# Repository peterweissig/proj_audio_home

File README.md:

# project_audio_home
Simple audio project for sound system @home

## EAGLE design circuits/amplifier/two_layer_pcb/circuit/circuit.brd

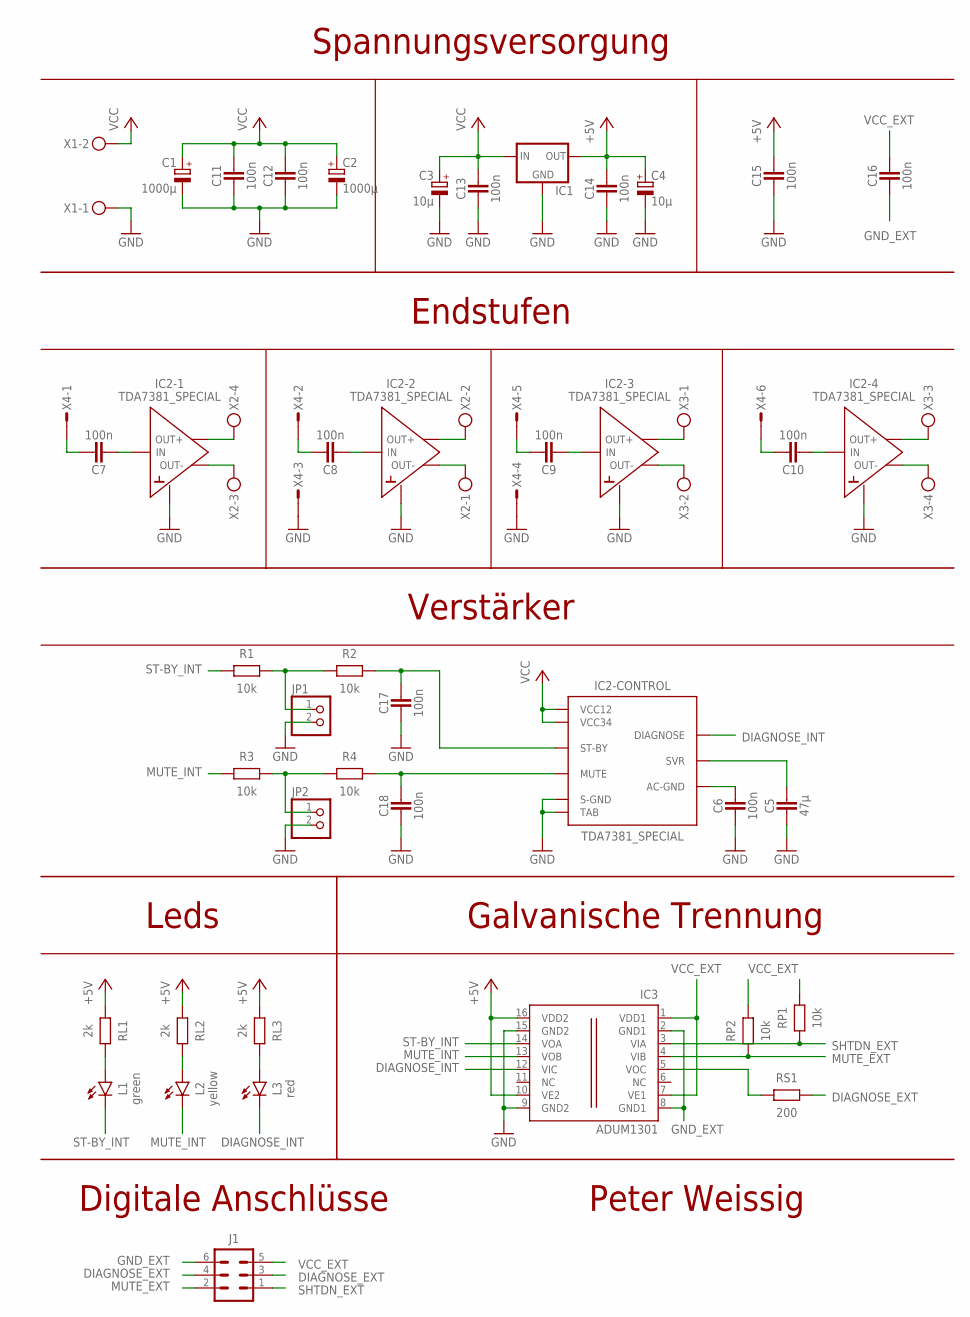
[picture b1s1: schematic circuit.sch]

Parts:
C1, C2: 1000µ; E5-10,5
C3, C4: 10µ; E2-5
C5: 47µ; SMD_2312S
C6, C11, C12, C13, C14, C15, C16: 100n; SMD_1206
C7, C8, C9, C10, C17, C18: 100n; C_THT_3
IC1: 78XXS
IC2: TDA7381_SPECIAL; IC_FLEXIWATT25_SPECIAL
IC3: ADUM1301; SO-16W
J1: STECKER_WANNE_6
JP1, JP2: PINHD-1X2; 1X02
L1: green; LED_3MM
L2: yellow; LED_3MM
L3: red; LED_3MM
R1, R2, R3, R4: 10k; SMD_1206
RL1, RL2, RL3: 2k; SMD_1206
RP1, RP2: 10k; SMD_1206
RS1: 200; SMD_1206
X1: STECKER_SPG_2
X2, X3: STECKER_SPG_4
X4: STECKER_MICROMATCH_6

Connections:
+5V: C4.+, C14.1, C15.1, IC1.OUT, IC3.10 (VE2), IC3.16 (VDD2), RL1.2, RL2.2, RL3.2
DIAGNOSE_EXT: J1.3, J1.4, RS1.2
DIAGNOSE_INT: IC2.25 (DIAGNOSE), IC3.12 (VIC), L3.K (C)
GND: C1.-, C2.-, C3.-, C4.-, C5.2, C6.2, C11.2, C12.2, C13.2, C14.2, C15.2, C17.1, C18.1, IC1.GND, IC2.1 (TAB), IC2.2 (GND), IC2.8 (GND), IC2.13 (S-GND), IC2.18 (GND), IC2.24 (GND), IC3.9 (GND2), IC3.15 (GND2), JP1.2, JP2.2, X1.1, X4.3, X4.4
GND_EXT: C16.2, IC3.2 (GND1), IC3.8 (GND1), J1.6
MUTE: C18.2, IC2.22 (MUTE), R4.2
MUTE_EXT: IC3.4 (VIB), J1.2, RP2.1
MUTE_INT: IC3.13 (VOB), L2.K (C), R3.1
unnamed: C7.2, IC2.11 (IN)
unnamed: C7.1, X4.1
unnamed: C8.1, X4.2
unnamed: C8.2, IC2.12 (IN)
unnamed: C9.1, X4.5
unnamed: C10.1, X4.6
unnamed: C9.2, IC2.15 (IN)
unnamed: C10.2, IC2.14 (IN)
unnamed: JP1.1, R1.2, R2.1
unnamed: C5.1, IC2.10 (SVR)
unnamed: C6.1, IC2.16 (AC-GND)
unnamed: L3.A, RL3.1
unnamed: L1.A, RL1.1
unnamed: JP2.1, R3.2, R4.1
unnamed: L2.A, RL2.1
unnamed: IC3.5 (VOC), RS1.1
OUT1+: IC2.9 (OUT+), X2.4
OUT1-: IC2.7 (OUT-), X2.3
OUT2+: IC2.5 (OUT+), X2.2
OUT2-: IC2.3 (OUT-), X2.1
OUT3+: IC2.17 (OUT+), X3.1
OUT3-: IC2.19 (OUT-), X3.2
OUT4+: IC2.21 (OUT+), X3.3
OUT4-: IC2.23 (OUT-), X3.4
SHTDN_EXT: IC3.3 (VIA), J1.1, RP1.1
ST-BY: C17.2, IC2.4 (ST-BY), R2.2
ST-BY_INT: IC3.14 (VOA), L1.K (C), R1.1
VCC: C1.+, C2.+, C3.+, C11.1, C12.1, C13.1, IC1.IN, IC2.6 (VCC12), IC2.20 (VCC34), X1.2
VCC_EXT: C16.1, IC3.1 (VDD1), IC3.7 (VE1), J1.5, RP1.2, RP2.2

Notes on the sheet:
Spannungsversorgung
Peter Weissig
Endstufen
Digitale Anschlüsse
Galvanische Trennung
Verstärker
Leds

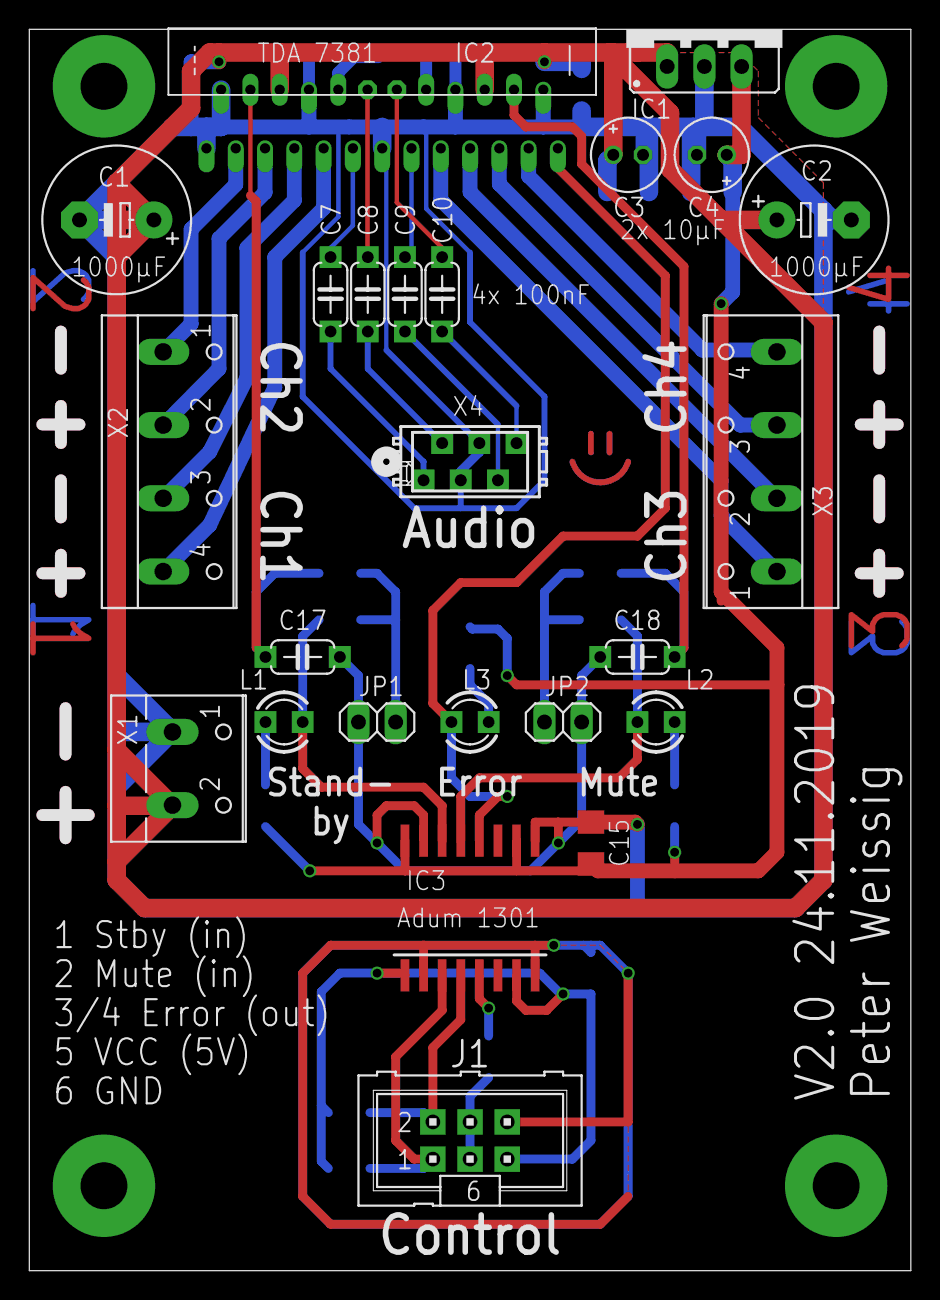
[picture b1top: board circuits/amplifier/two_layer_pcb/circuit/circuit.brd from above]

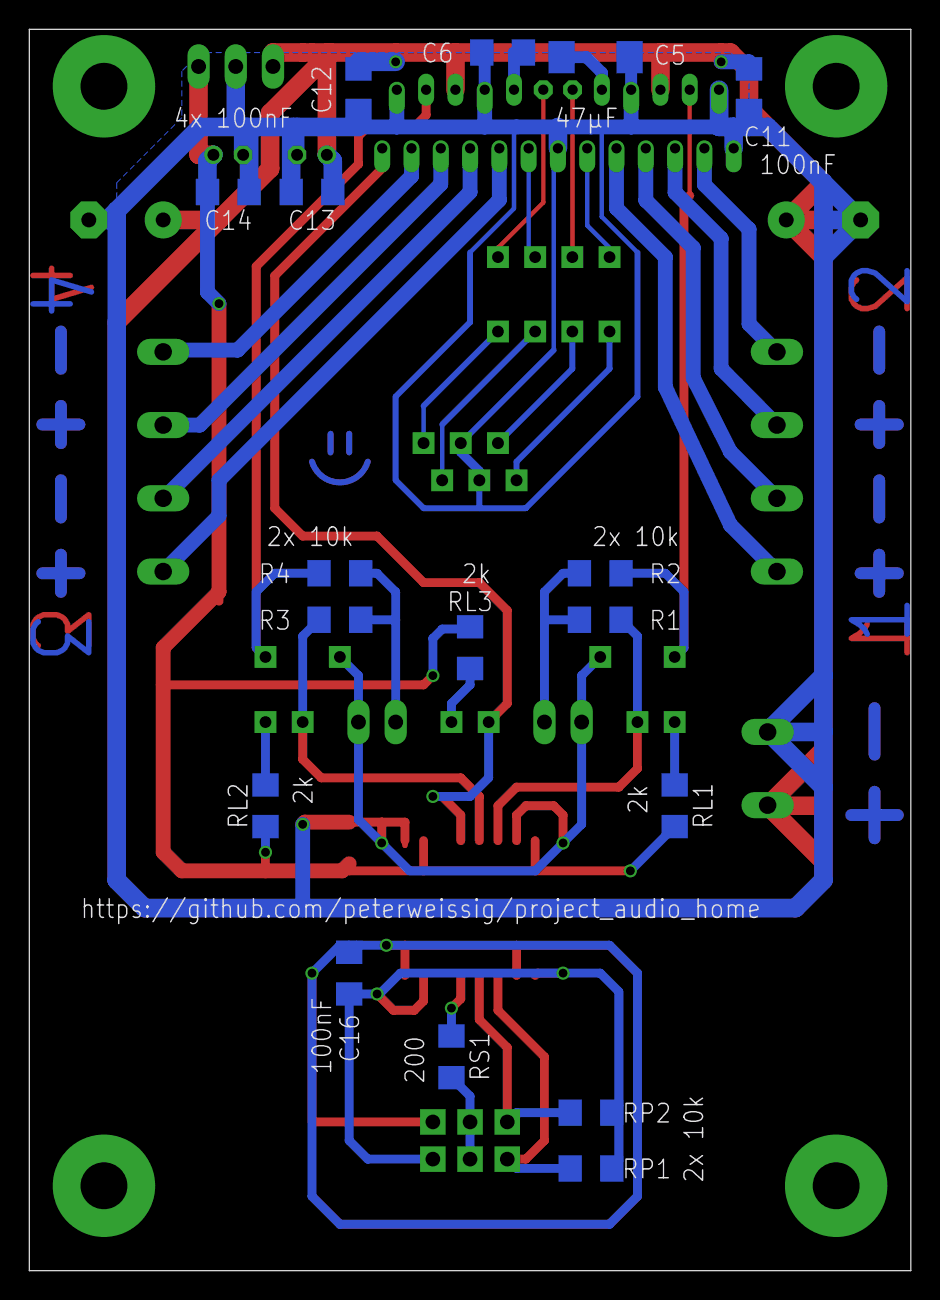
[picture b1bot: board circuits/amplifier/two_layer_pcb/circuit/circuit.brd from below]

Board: 2 copper layers, 60.2 x 84.8 mm, 41 parts (17 on the bottom side), 37 nets.

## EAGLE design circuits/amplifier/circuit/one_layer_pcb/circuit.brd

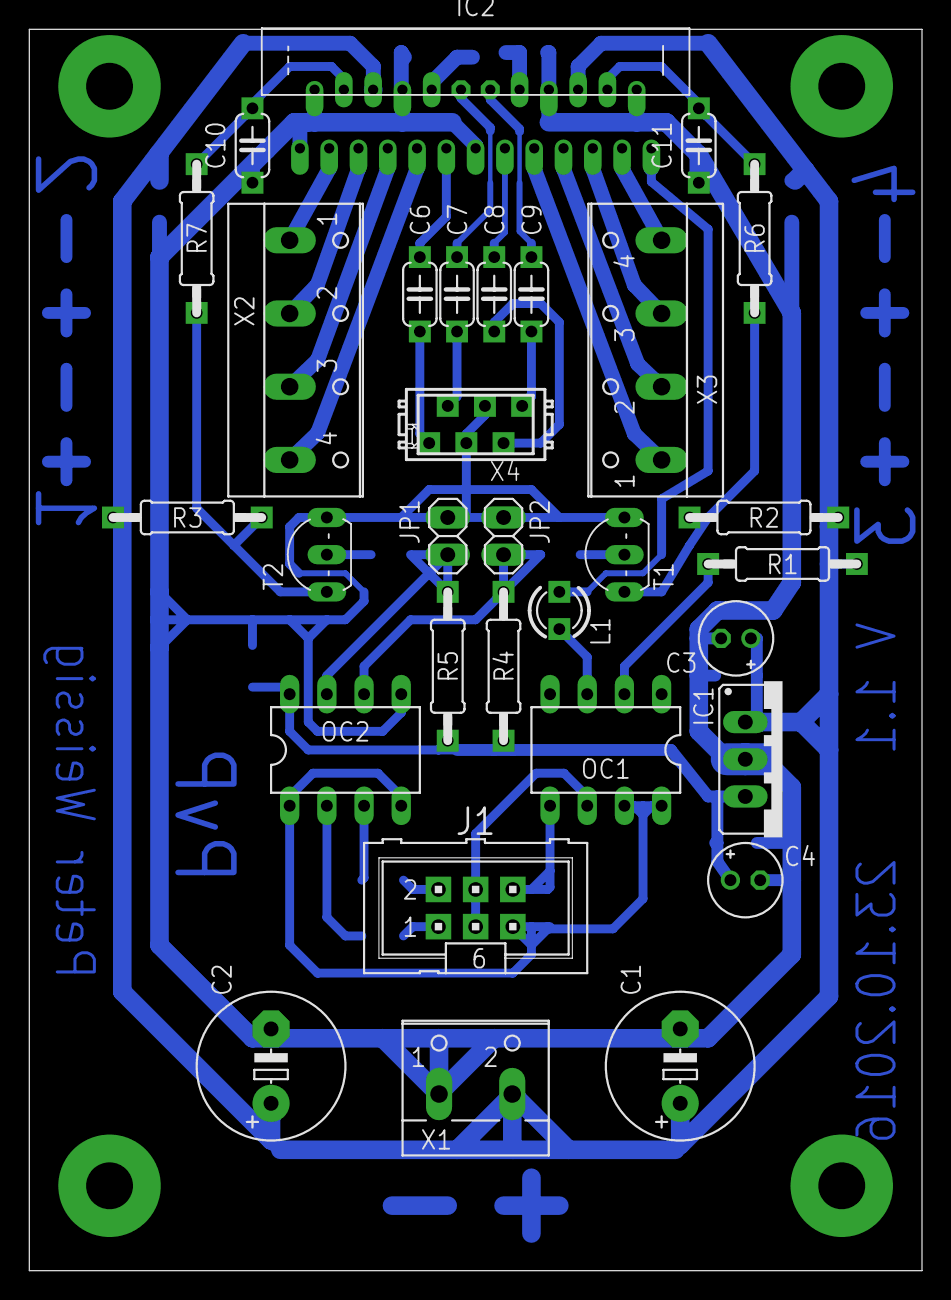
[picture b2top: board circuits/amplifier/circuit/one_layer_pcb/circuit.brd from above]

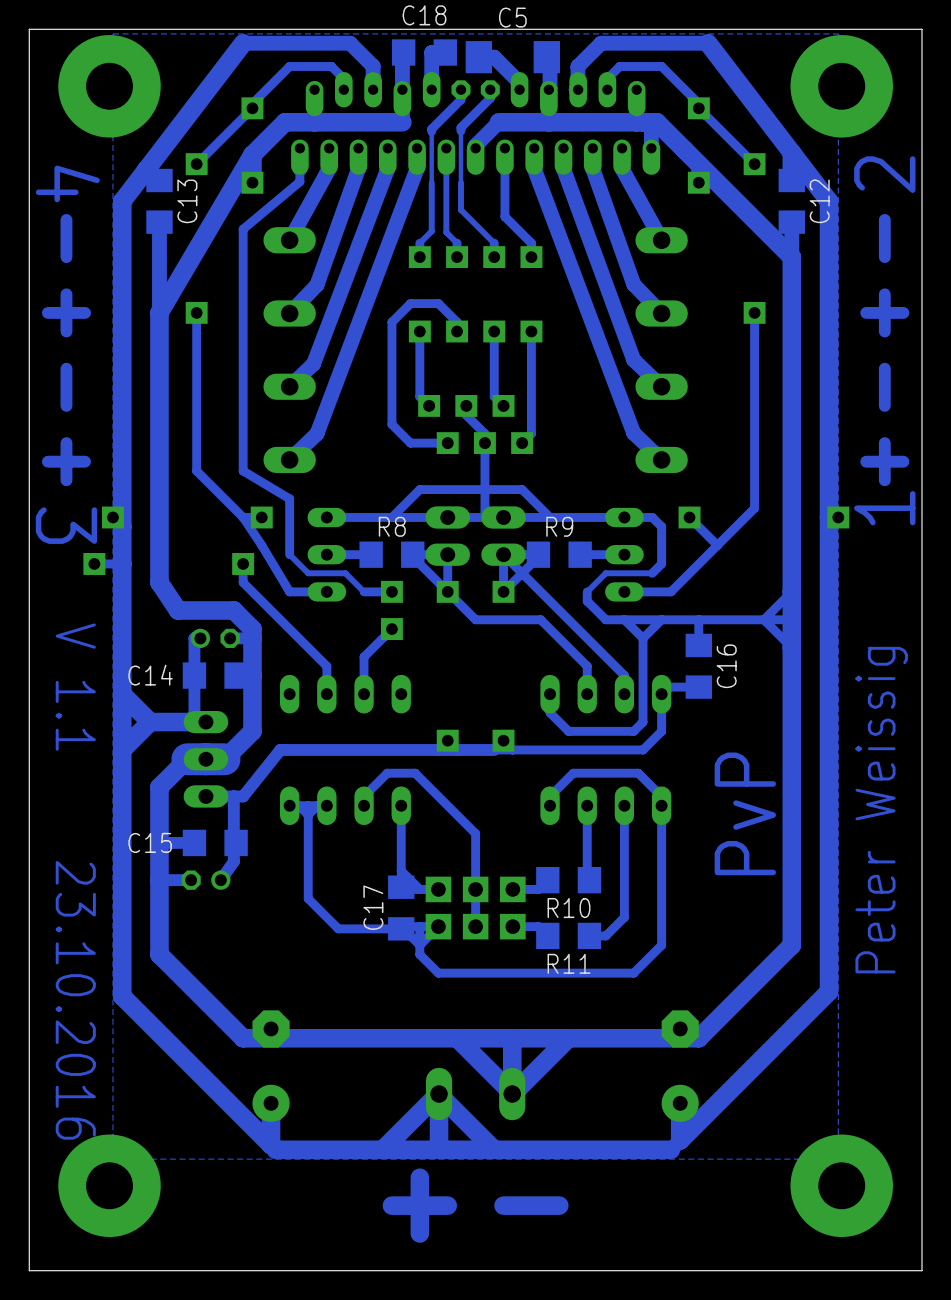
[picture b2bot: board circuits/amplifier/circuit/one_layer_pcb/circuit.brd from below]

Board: 2 copper layers, 61.0 x 84.8 mm, 43 parts (12 on the bottom side), 39 nets.

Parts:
C1, C2: 1000µ; E5-10,5
C3, C4: 10µ; E2-5
C5: 47µ; SMD_2312S
C6, C7, C8, C9, C10, C11: 100n; C_THT_3
C12, C13, C14, C15, C16, C17, C18: 100n; SMD_1206
IC1: 78XXS
IC2: TDA7381_SPECIAL; IC_FLEXIWATT25_SPECIAL
J1: STECKER_WANNE_6
JP1, JP2: 1X02
L1: LED_3MM
OC1: COUPLER_HCPL2601; IC_DIL08
OC2: COUPLER_HCPL2631; IC_DIL08
R1: 1k; R_THT_4
R2, R3, R4, R5, R6, R7: 10k; R_THT_4
R8, R9: 10k; SMD_1206
R10, R11: 150; SMD_1206
T1, T2: TO92-CBE
X1: STECKER_SPG_2
X2, X3: STECKER_SPG_4
X4: STECKER_MICROMATCH_6

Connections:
+5V: C4.+, C15.1, C16.1, IC1.OUT, OC2.8, R4.2, R5.2
DIAGNOSE_EXT: J1.3, J1.4, OC1.6
GND: C1.-, C2.-, C3.-, C4.-, C5.2, C10.1, C11.1, C12.2, C13.2, C14.2, C15.2, C16.2, C18.2, IC1.GND, IC2.1, IC2.2, IC2.8, IC2.13, IC2.18, IC2.24, JP1.1, JP2.1, OC2.5, T1.E, T2.E, X1.1, X4.3, X4.4
GND_EXT: C17.2, J1.6, OC1.5
MUTE_EXT: J1.2, R10.2
unnamed: C6.2, IC2.11
unnamed: C6.1, X4.1
unnamed: C7.1, X4.2
unnamed: C7.2, IC2.12
unnamed: C8.1, X4.5
unnamed: C9.1, X4.6
unnamed: C8.2, IC2.15
unnamed: C9.2, IC2.14
unnamed: C10.2, IC2.4, R7.1
unnamed: C11.2, IC2.22, R6.1
unnamed: C5.1, IC2.10
unnamed: C18.1, IC2.16
unnamed: IC2.25, L1.K
unnamed: L1.A, OC1.3
unnamed: R2.2, R6.2, T1.C
unnamed: JP2.2, OC2.6, R4.1, R8.1
unnamed: R8.2, T1.B
unnamed: OC1.2, R1.1
unnamed: R3.2, R7.2, T2.C
unnamed: JP1.2, OC2.7, R5.1, R9.1
unnamed: R9.2, T2.B
unnamed: OC2.2, R11.1
unnamed: OC2.3, R10.1
OUT1+: IC2.9, X2.4
OUT1-: IC2.7, X2.3
OUT2+: IC2.5, X2.2
OUT2-: IC2.3, X2.1
OUT3+: IC2.17, X3.1
OUT3-: IC2.19, X3.2
OUT4+: IC2.21, X3.3
OUT4-: IC2.23, X3.4
SHTDN_EXT: J1.1, R11.2
VCC: C1.+, C2.+, C3.+, C12.1, C13.1, C14.1, IC1.IN, IC2.6, IC2.20, R1.2, R2.1, R3.1, X1.2
VCC_EXT: C17.1, J1.5, OC1.7, OC1.8, OC2.1, OC2.4

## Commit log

2019-11-24 moved files of old one-sided pcb (audio-driver)
2019-11-24 added new two-sided version of audio-driver + exported images + exported elecrow-data + todo: part list
2019-11-24 updated gitgingore
2019-12-15 switched layer of some visible marks (so they are printed on the circuit boards)
